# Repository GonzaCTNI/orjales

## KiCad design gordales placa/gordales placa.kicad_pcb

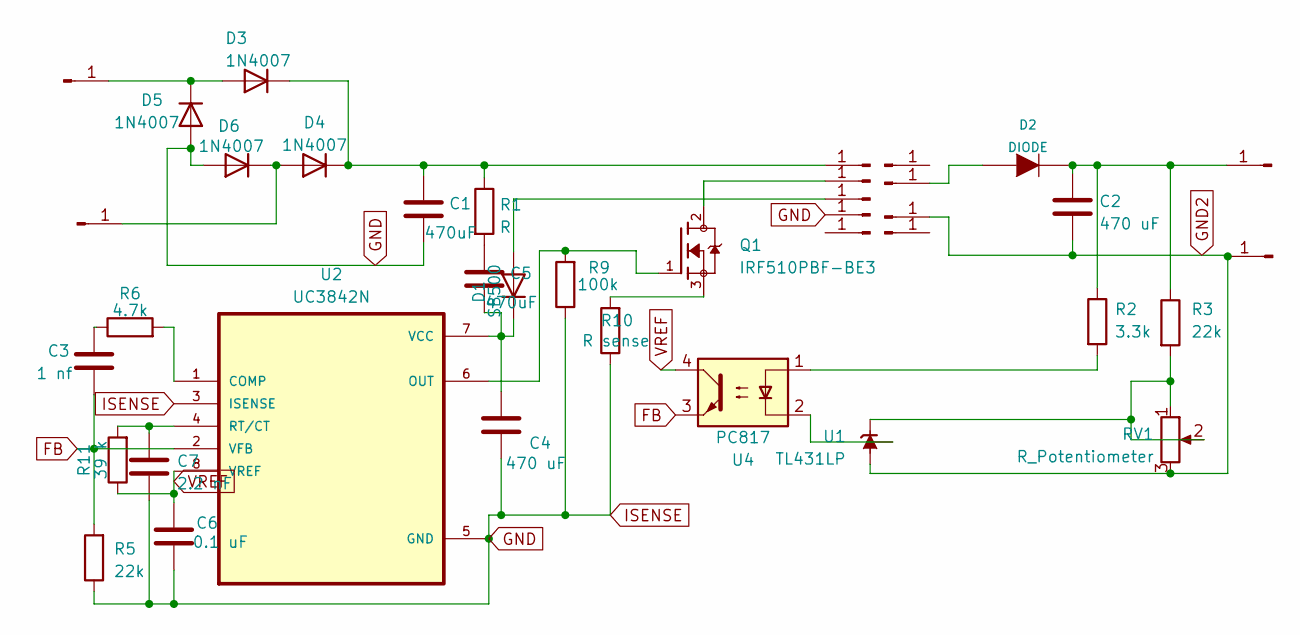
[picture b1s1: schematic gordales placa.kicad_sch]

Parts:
C1: 470uF; CP_Radial_D8.0mm_P5.00mm
C2: 470 uF; CP_Radial_D8.0mm_P2.50mm
C3: 1 nf; CP_Radial_D4.0mm_P2.00mm
C4: 470 uF; C_Axial_L3.8mm_D2.6mm_P10.00mm_Horizontal
C5: 470uF; CP_Radial_D8.0mm_P2.50mm
C6: 0.1 uF; CP_Radial_D4.0mm_P2.00mm
C7: 2.2 nF; CP_Radial_D4.0mm_P2.00mm
D1: SB500; D_DO-41_SOD81_P12.70mm_Horizontal
D2: DIODE; D_DO-41_SOD81_P10.16mm_Horizontal
D3, D4, D5, D6: 1N4007; D_DO-41_SOD81_P10.16mm_Horizontal
J1, J2, J3, J4, J5, J6, J7, J8, J9, J10, J11, J12, J13: Conn_01x01_Pin; PinHeader_1x01_P2.54mm_Vertical
Q1: IRF510PBF-BE3; TO254P1051X465X1931-3; PARTREV D
R1: R; R_Axial_DIN0207_L6.3mm_D2.5mm_P10.16mm_Horizontal
R2: 3.3k; R_Axial_DIN0207_L6.3mm_D2.5mm_P10.16mm_Horizontal
R3, R5: 22k; R_Axial_DIN0207_L6.3mm_D2.5mm_P10.16mm_Horizontal
R6: 4.7k; R_Axial_DIN0207_L6.3mm_D2.5mm_P10.16mm_Horizontal
R9: 100k; R_Axial_DIN0207_L6.3mm_D2.5mm_P10.16mm_Horizontal
R10: R sense; R_Axial_DIN0207_L6.3mm_D2.5mm_P10.16mm_Horizontal
R11: 39 k; R_Axial_DIN0207_L6.3mm_D2.5mm_P10.16mm_Horizontal
RV1: R_Potentiometer; Potentiometer_Alps_RK09Y11_Single_Horizontal
U1: TL431LP; PinHeader_1x03_P2.54mm_Vertical
U2: UC3842N
U4: PC817; DIP-4_W7.62mm

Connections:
FB: C3.2, R5.2, U2.2 (VFB), U4.3
GND: C1.2, C4.2, C6.2, C7.2, D5.2 (A), D6.2 (A), J2.1, R5.1, R9.1, R10.1, U2.3 (ISENSE), U2.5 (GND)
GND2: C2.2, J7.1, J8.1, RV1.3, U1.2 (A)
unnamed: C3.1, R6.1
unnamed: C5.1, R1.2
unnamed: D1.2 (A), J3.1
unnamed: C4.1, C5.2, D1.1 (K), U2.7 (VCC)
unnamed: D2.1 (A), J9.1
unnamed: C2.1, D2.2 (K), J13.1, R2.1, R3.1
unnamed: D3.2 (A), D5.1 (K), J11.1
unnamed: C1.1, D3.1 (K), D4.1 (K), J5.1, R1.1
unnamed: D4.2 (A), D6.1 (K), J12.1
unnamed: J4.1, Q1.2
unnamed: Q1.3, R10.2
unnamed: R2.2, U4.1
unnamed: R3.2, RV1.1, RV1.2, U1.3 (K)
unnamed: U1.1 (REF), U4.2
unnamed: R6.2, U2.1 (COMP)
unnamed: Q1.1, R9.2, U2.6 (OUT)
unnamed: C7.1, R11.2, U2.4 (RT/CT)
VREF: C6.1, R11.1, U2.8 (VREF), U4.4

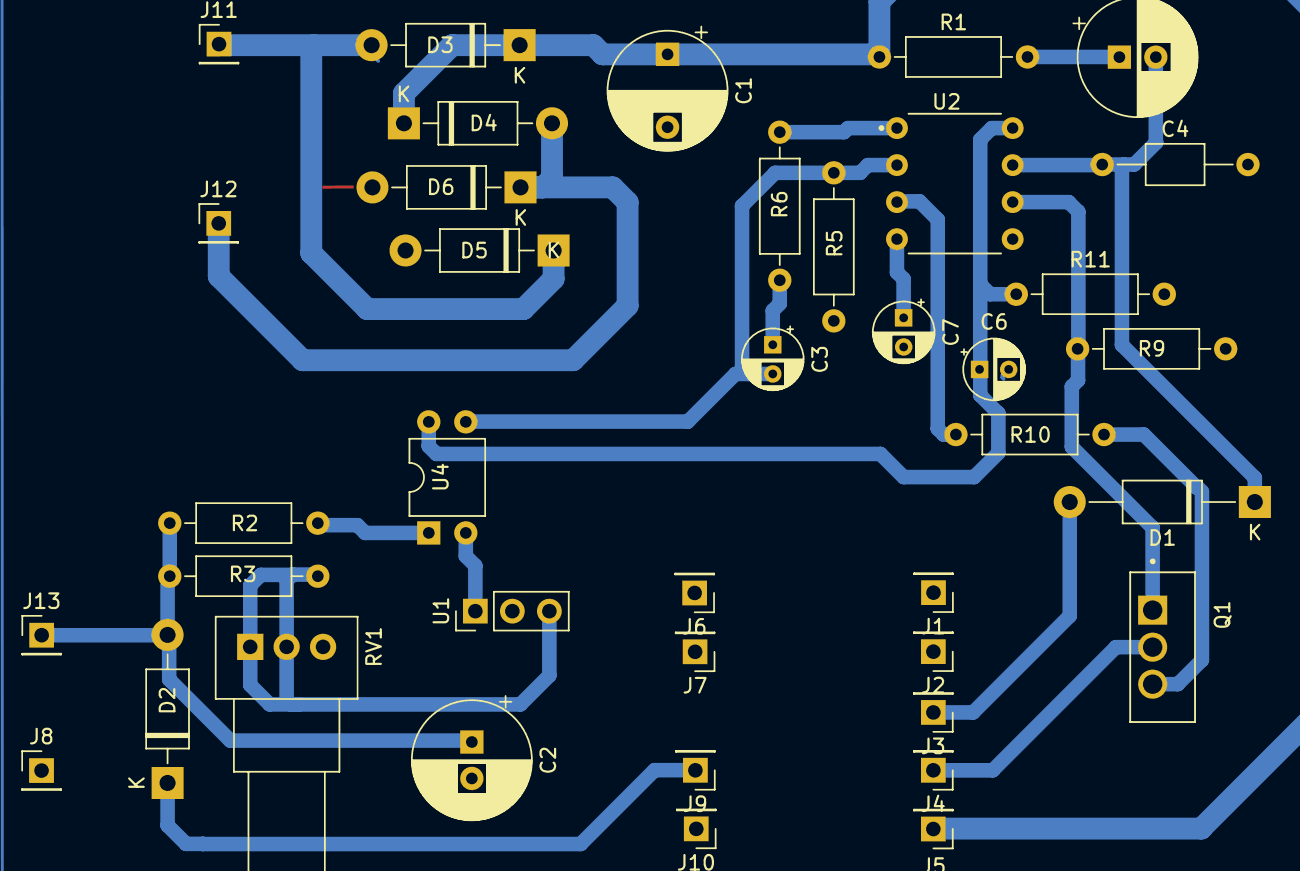
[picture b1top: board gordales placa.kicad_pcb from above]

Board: 2 copper layers, 39 parts (0 on the bottom side), 21 nets.
